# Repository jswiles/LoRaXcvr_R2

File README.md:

# LoRa Transceiver

LoRa Transceiver PCB for LoRa Remote Monitor System

- STM32L15x MPU : 
    - 256K FlashMemory
    - 32K SRAM
    - RTC Support - 32Khz Crystal

- HopeRF RFM95W LoRa Module 
    - US 915Mhz (FCC certified)

- TTL RS-232 Debug Port

- ST-LINK SWDIO Programming header

- Input Voltage   
    - 5.2 to 10 volts DC (500mA max)

Revision 1 

Revision 2 3D Model

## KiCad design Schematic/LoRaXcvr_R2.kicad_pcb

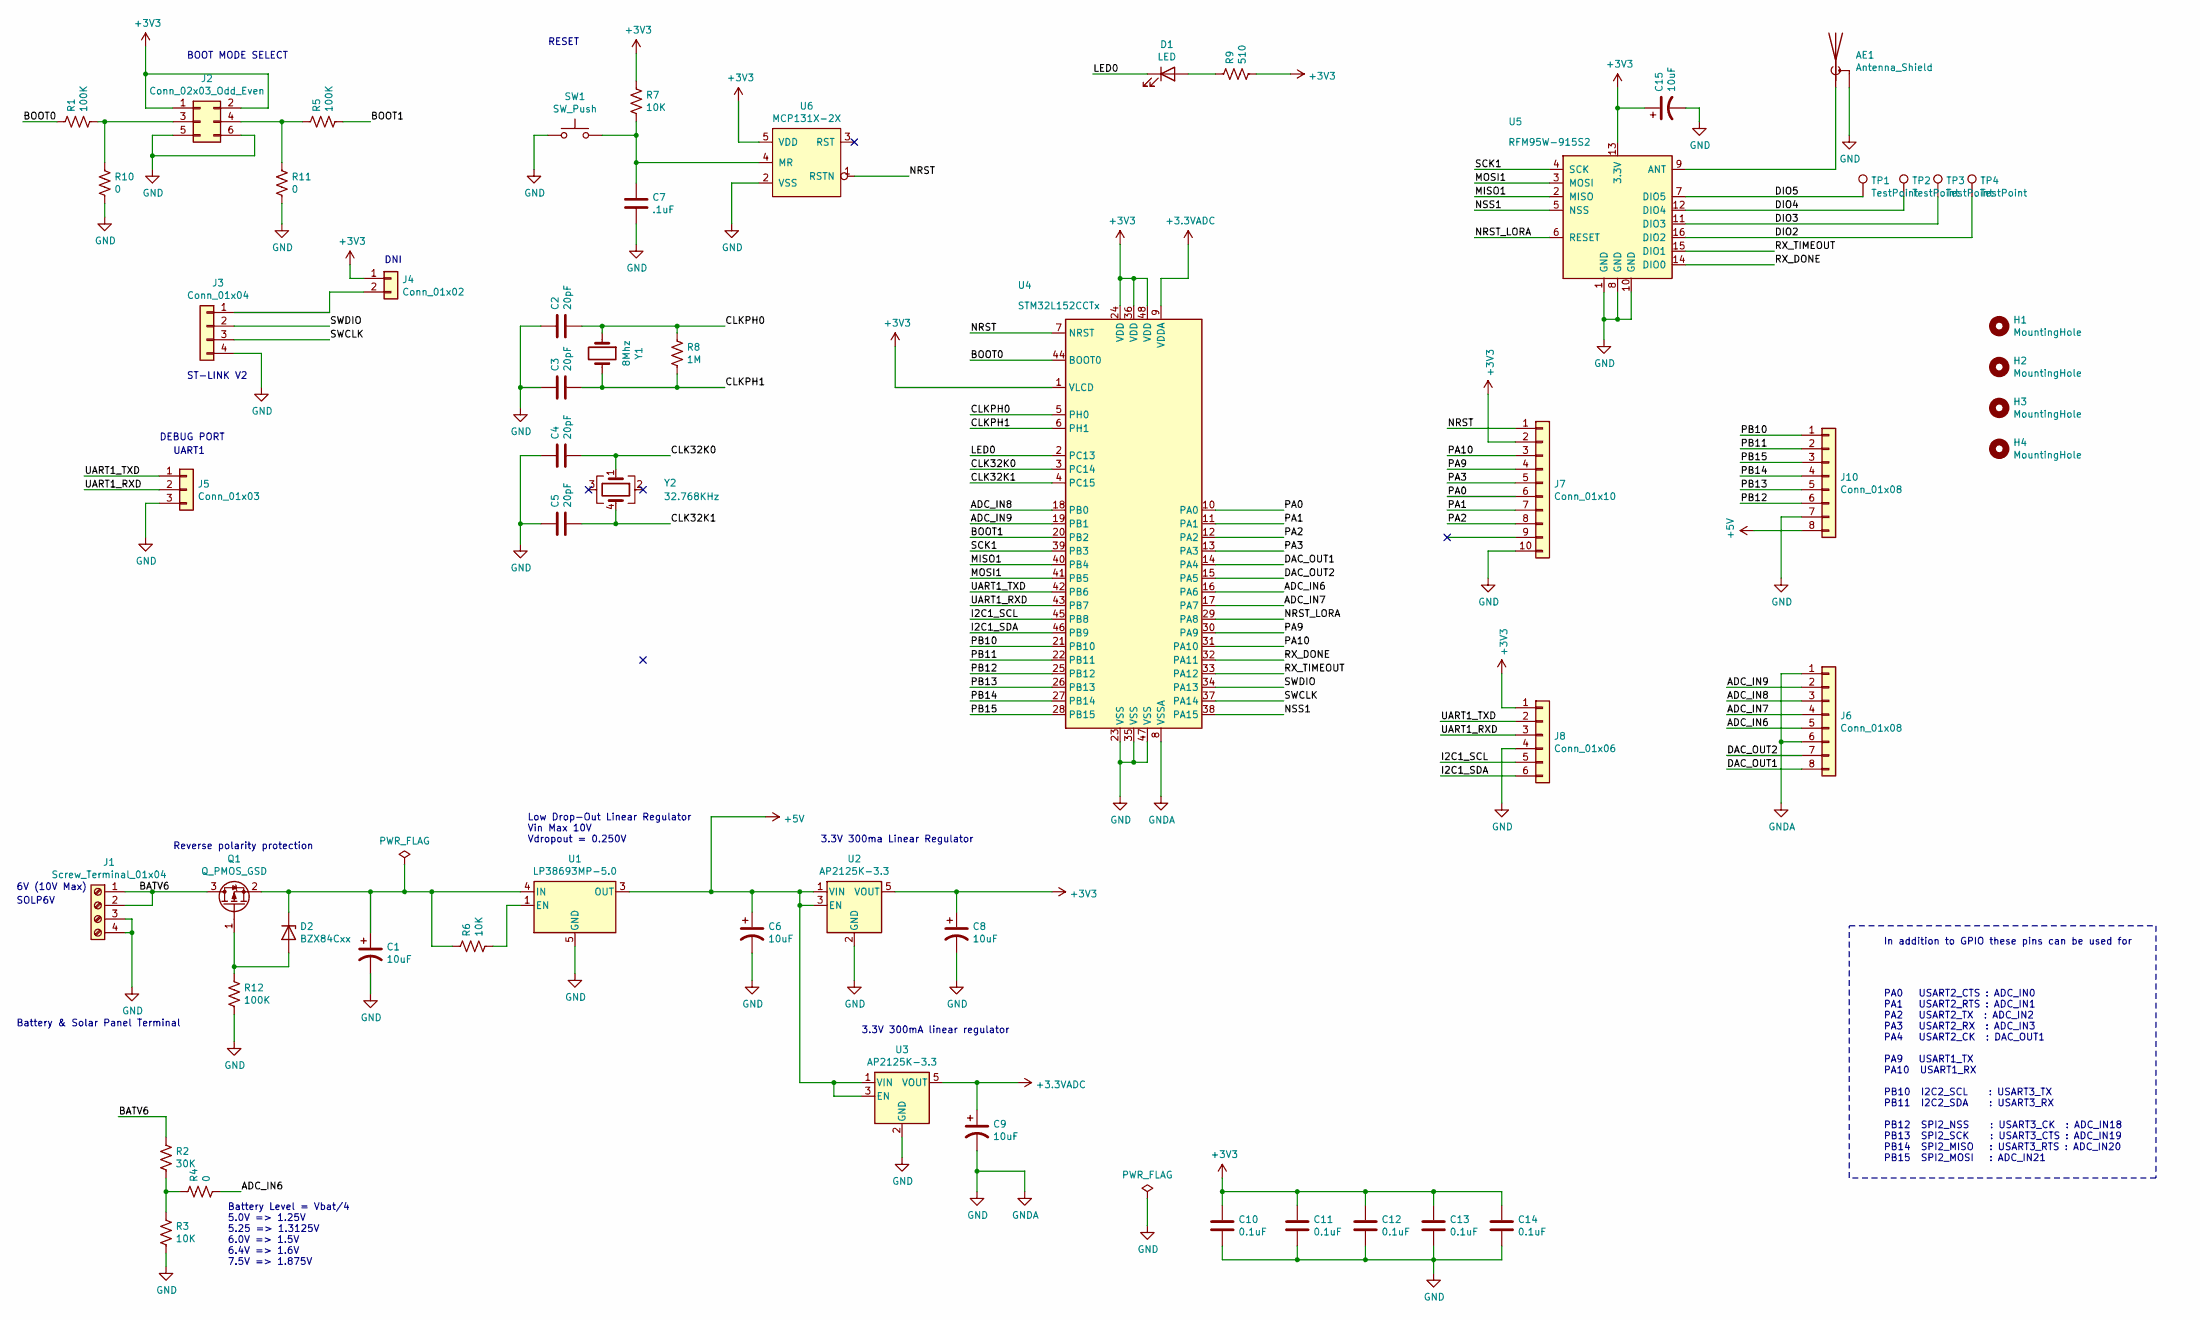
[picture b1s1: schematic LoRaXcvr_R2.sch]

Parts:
AE1: Antenna_Shield; U.FL-COAX; DigiKey CONUFL001-SMD-T
C1: 10uF; CP_EIA-6032-20_AVX-F_Pad2.25x2.35mm_HandSolder; DigiKey 478-5804-1-ND
C2, C3, C4, C5: 20pF; C_0805_2012Metric; DigiKey 399-8030-1-ND
C6: 10uF; CP_EIA-6032-20_AVX-F_Pad2.25x2.35mm_HandSolder
C7: .1uF; C_0805_2012Metric; DigiKey 311-1140-1-ND
C8, C9, C15: 10uF; CP_EIA-3216-18_Kemet-A_Pad1.58x1.35mm_HandSolder; DigiKey 399-3684-1-ND
C10, C11, C12, C13, C14: 0.1uF; C_0805_2012Metric; DigiKey 311-1140-1-ND
D1: LED; LED_0805_2012Metric; DigiKey 754-1795-1-ND
D2: BZX84Cxx; D_SOT-23_ANK; DigiKey 353-BZX84C10HE3-TPCT-ND
H1, H2, H3, H4: MountingHole; MountingHole_2.5mm
J1: Screw_Terminal_01x04; TerminalBlock_TE_282834-4_1x04_P2.54mm_Horizontal; DigiKey ED10563-ND
J2: Conn_02x03_Odd_Even; PinHeader_2x03_P2.54mm_Vertical; DigiKey 609-6338-ND
J3: Conn_01x04; PinHeader_1x04_P2.54mm_Horizontal; DigiKey S1111EC-40-ND
J4: Conn_01x02; PinHeader_1x02_P2.54mm_Vertical; DigiKey S1011EC-40-ND
J5: Conn_01x03; PinHeader_1x03_P2.54mm_Horizontal; DigiKey S1111EC-40-ND
J6, J10: Conn_01x08; PinSocket_1x08_P2.54mm_Vertical; DigiKey S1011EC-40-ND
J7: Conn_01x10; PinSocket_1x10_P2.54mm_Vertical; DigiKey S1011EC-40-ND
J8: Conn_01x06; PinSocket_1x06_P2.54mm_Vertical; DigiKey S1011EC-40-ND
Q1: Q_PMOS_GSD; SOT-23; DigiKey SI2307CDS-T1-E3CT-ND
R1, R5, R12: 100K; R_0805_2012Metric; DigiKey 541-CRCW0805100KJNEBCT-ND
R2: 30K; R_0805_2012Metric; DigiKey 541-30KACT-ND
R3, R6, R7: 10K; R_0805_2012Metric; DigiKey RMCF0805JT10K0CT-ND
R4: 0; R_0805_2012Metric; DigiKey RMCF0805ZT0R00CT-ND
R8: 1M; R_0805_2012Metric; DigiKey 541-1.0MACT-ND
R9: 510; R_0805_2012Metric; DigiKey 541-510ACT-ND
R10, R11: 0; R_0805_2012Metric
SW1: SW_Push; SW_Push_1P1T_NO_CK_KSC6xxJ; DigiKey CKN9112CT-ND
TP1, TP2, TP3, TP4: TestPoint; TestPoint_THTPad_D1.0mm_Drill0.5mm
U1: LP38693MP-5.0; SOT-223-5; DigiKey LP38693MPX-5.0/NOPBCT-ND
U2: AP2125K-3.3; SOT-23-5_HandSoldering; DigiKey AP2125K-3.3TRG1DICT-ND
U3: AP2125K-3.3; SOT-23-5_HandSoldering; DigiKey AP2127K-3.3TRG1DICT-ND
U4: STM32L152CCTx; LQFP-48_7x7mm_P0.5mm; DigiKey 497-17533-ND
U5: RFM95W-915S2; HOPERF_RFM9XW_SMD; DigiKey RFM95W-915S2-ND
U6: MCP131X-2X; SOT-23-5_HandSoldering; DigiKey MCP1319MT-29LE/OTCT-ND
Y1: 8Mhz; Crystal_SMD_HC49-SD_HandSoldering; DigiKey 535-10212-1-ND
Y2: 32.768KHz; Crystal_SMD_Abracon_ABS25-4Pin_8.0x3.8mm; DigiKey 535-13425-1-ND

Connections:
+3.3VADC: C9.1, U3.5 (VOUT), U4.9 (VDDA)
+3V3: C8.1, C10.1, C11.1, C12.1, C13.1, C14.1, C15.1, J2.1, J2.2, J4.1, J7.2, J8.1, R7.1, R9.2, U2.5 (VOUT), U4.1 (VLCD), U4.24 (VDD), U4.36 (VDD), U4.48 (VDD), U5.13 (3.3V), U6.5 (VDD)
+5V: C6.1, J10.8, U1.3 (OUT), U2.1 (VIN), U2.3 (EN), U3.1 (VIN), U3.3 (EN)
/ADC_IN6: J6.5, R4.2, U4.16 (PA6)
/ADC_IN7: J6.4, U4.17 (PA7)
/ADC_IN8: J6.3, U4.18 (PB0)
/ADC_IN9: J6.2, U4.19 (PB1)
/BATV6: J1.1, J1.2, Q1.3 (D), R2.1
/BOOT0: R1.1, U4.44 (BOOT0)
/BOOT1: R5.2, U4.20 (PB2)
/CLK32K0: C4.2, U4.3 (PC14), Y2.1
/CLK32K1: C5.2, U4.4 (PC15), Y2.4
/CLKPH0: C2.2, R8.1, U4.5 (PH0), Y1.1
/CLKPH1: C3.2, R8.2, U4.6 (PH1), Y1.2
/DAC_OUT1: J6.8, U4.14 (PA4)
/DAC_OUT2: J6.7, U4.15 (PA5)
/DIO2: TP4.1, U5.16 (DIO2)
/DIO3: TP3.1, U5.11 (DIO3)
/DIO4: TP2.1, U5.12 (DIO4)
/DIO5: TP1.1, U5.7 (DIO5)
/I2C1_SCL: J8.5, U4.45 (PB8)
/I2C1_SDA: J8.6, U4.46 (PB9)
/LED0: D1.1 (K), U4.2 (PC13)
/MISO1: U4.40 (PB4), U5.2 (MISO)
/MOSI1: U4.41 (PB5), U5.3 (MOSI)
/NRST: J7.1, U4.7 (NRST), U6.1 (RSTN)
/NRST_LORA: U4.29 (PA8), U5.6 (RESET)
/NSS1: U4.38 (PA15), U5.5 (NSS)
/PA0: J7.6, U4.10 (PA0)
/PA1: J7.7, U4.11 (PA1)
/PA2: J7.8, U4.12 (PA2)
/PA3: J7.5, U4.13 (PA3)
/PA9: J7.4, U4.30 (PA9)
/PA10: J7.3, U4.31 (PA10)
/PB10: J10.1, U4.21 (PB10)
/PB11: J10.2, U4.22 (PB11)
/PB12: J10.6, U4.25 (PB12)
/PB13: J10.5, U4.26 (PB13)
/PB14: J10.4, U4.27 (PB14)
/PB15: J10.3, U4.28 (PB15)
/RX_DONE: U4.32 (PA11), U5.14 (DIO0)
/RX_TIMEOUT: U4.33 (PA12), U5.15 (DIO1)
/SCK1: U4.39 (PB3), U5.4 (SCK)
/SWCLK: J3.3, U4.37 (PA14)
/SWDIO: J3.2, U4.34 (PA13)
/UART1_RXD: J5.2, J8.3, U4.43 (PB7)
/UART1_TXD: J5.1, J8.2, U4.42 (PB6)
GND: AE1.2 (Shield), C1.2, C2.1, C3.1, C4.1, C5.1, C6.2, C7.2, C8.2, C9.2, C10.2, C11.2, C12.2, C13.2, C14.2, C15.2, J1.3, J1.4, J2.5, J2.6, J3.4, J5.3, J6.1, J6.6, J7.10, J8.4, J10.7, R3.2, R10.2, R11.2, R12.2, SW1.1, U1.5 (GND), U2.2 (GND), U3.2 (GND), U4.8 (VSSA), U4.23 (VSS), U4.35 (VSS), U4.47 (VSS), U5.1 (GND), U5.8 (GND), U5.10 (GND), U6.2 (VSS)
unnamed: AE1.1 (A), U5.9 (ANT)
unnamed: C1.1, D2.1 (K), Q1.2 (S), R6.1, U1.4 (IN)
unnamed: C7.1, R7.2, SW1.2, U6.4 (MR)
unnamed: D1.2 (A), R9.1
unnamed: D2.2 (A), Q1.1 (G), R12.1
unnamed: J2.3, R1.2, R10.1
unnamed: J2.4, R5.1, R11.1
unnamed: J3.1, J4.2
unnamed: R2.2, R3.1, R4.1
unnamed: R6.2, U1.1 (EN)

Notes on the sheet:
UART1
DEBUG PORT
Battery & Solar Panel Terminal
6V (10V Max)
SOLP6V
PA0 USART2_CTS : ADC_IN0 PA1 USART2_RTS : ADC_IN1 PA2 USART2_TX : ADC_IN2 PA3 USART2_RX : ADC_IN3 PA4 USART2_CK : DAC_OUT1 PA9 USART1_TX PA10 USART1_RX PB10 I2C2_SCL : USART3_TX PB11 I2C2_SDA : USART3_RX PB12 SPI2_NSS : USART3_CK : ADC_IN18 PB13 SPI2_SCK : USART3_CTS : ADC_IN19 PB14 SPI2_MISO : USA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
In addition to GPIO these pins can be used for
ST-LINK V2
BOOT MODE SELECT
RESET
3.3V 300ma Linear Regulator
3.3V 300mA linear regulator
Low Drop-Out Linear Regulator Vin Max 10V Vdropout = 0.250V
Battery Level = Vbat/4 5.0V => 1.25V 5.25 => 1.3125V 6.0V => 1.5V 6.4V => 1.6V 7.5V => 1.875V
DNI
Reverse polarity protection

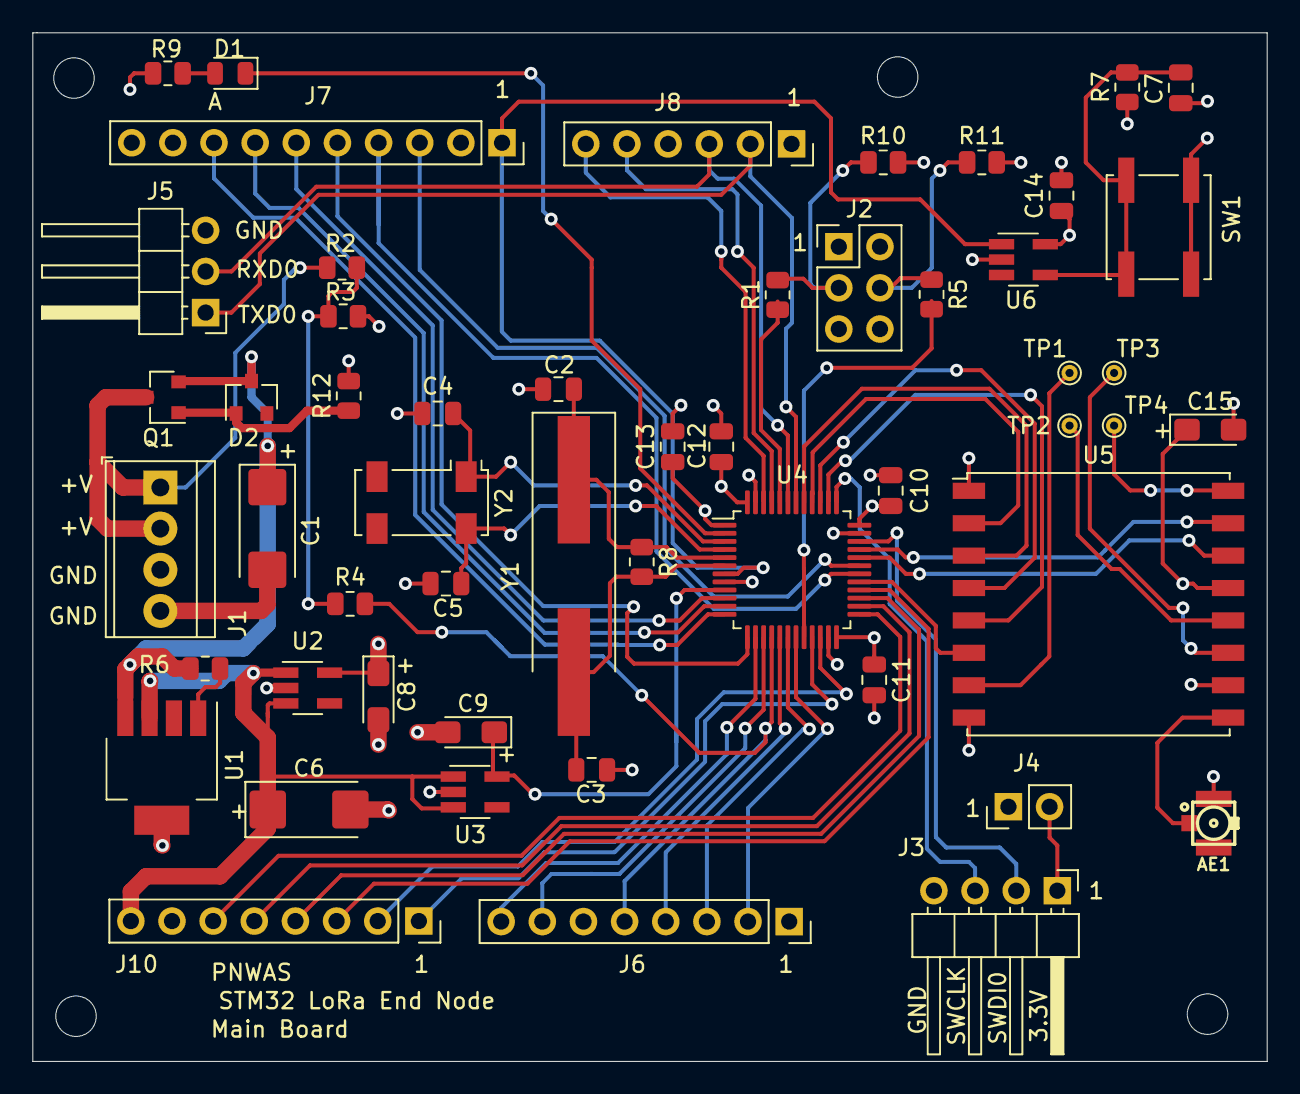
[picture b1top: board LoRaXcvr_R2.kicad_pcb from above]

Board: 4 copper layers, 76.2 x 63.5 mm, 57 parts (0 on the bottom side), 58 nets.

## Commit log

2022-08-01 Add BOM
2022-08-01 Deleted Photo
2022-08-01 Added PCB (gerber file) directory
2022-08-01 Added Schematic directory
2022-08-01 Added Documents directory
2022-08-02 Updated R2 schematic and documents
